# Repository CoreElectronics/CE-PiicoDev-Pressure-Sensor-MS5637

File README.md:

# PiicoDev® Pressure Sensor MS5637

This is the repo for the Core Electronics [PiicoDev Pressure Sensor](https://core-electronics.com.au/catalog/product/view/sku/CE07832).

Our PiicoDev® Pressure Sensor is perfect for measuring barometric pressure or infering altitude from air pressure - the on-board MS5637 is capable of measuring differences as small as 13cm! The accurate, MEMs pressure sensor is very sensitive, factory calibrated, low power and easy to use - forfect for home weather stations, detecting changes in altitude or pneumatic-based control projects.

**Features**

- Accurate air pressure measurements
- PiicoDev connector, compatible with Qwiic and STEMMA QT (3.3V only)
- 2.54mm breakout for breadboarding/prototyping
- Manufactured and [supported](https://core-electronics.com.au/contacts/) in Australia by Core Electronics
- [Getting Started Guides](https://core-electronics.com.au/catalog/product/view/sku/CE07832#guides)

**Technical Specifications**

- I2C address: 0x76
- Dimensions: 25.4x25.4mm
- Mounting Holes: 2x M2.5
- MS5637:
  - Operating range: 300 to 1200 hPa, -40 to 85°C
  - Error band at 25°C: ±2 hPa

## License
This project is open source - please review the LICENSE.md file for further licensing information.

If you have any technical questions, or concerns about licensing, please contact technical support on the [Core Electronics forums](https://forum.core-electronics.com.au/).

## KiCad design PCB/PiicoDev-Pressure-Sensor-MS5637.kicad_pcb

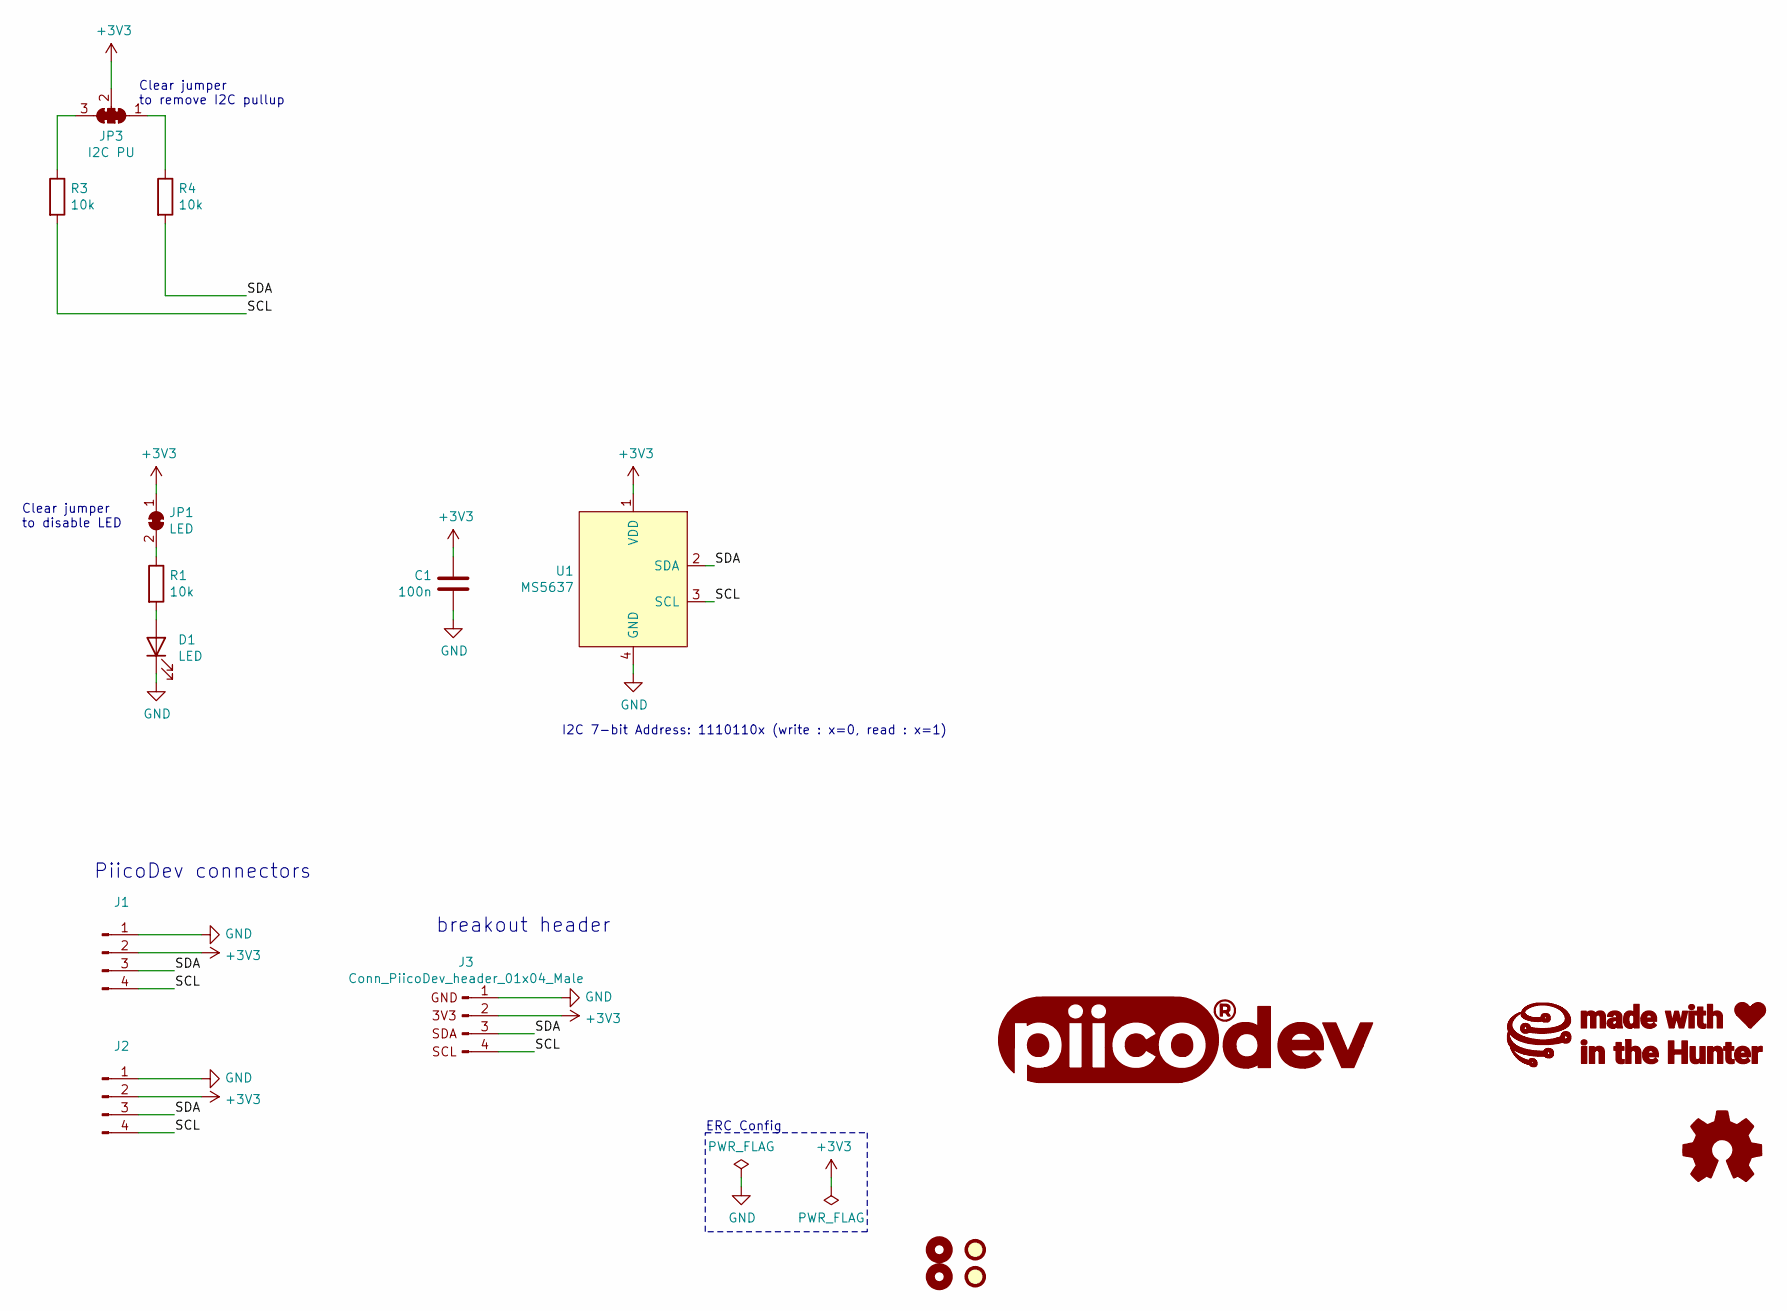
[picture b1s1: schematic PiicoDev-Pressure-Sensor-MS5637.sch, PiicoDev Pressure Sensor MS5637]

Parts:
C1: 100n; C_0402_1005Metric
D1: LED; LED_0603_1608Metric
FID1, FID2: Fiducial; Fiducial_1mm_Mask2mm
G1: LOGO_CoreElectronics_no-text; CoreElectronics_logo_5mm
G2: LOGO_piico; piicodev_logo_14.2x3.4mm
G3: LOGO_made-with-love; piicodev_logo_14.2x3.4mm
H1, H4: MountingHole; MountingHole_2.7mm_M2.5_PadClearance_1.2
J1, J2: JST_SH_SM04B-SRSS-TB_1x04-1MP_P1.00mm_Horizontal
J3: Conn_PiicoDev_header_01x04_Male; PiicoDev_header_4pin
JP1: LED; SolderJumper-2_P1.3mm_Bridged_RoundedPad1.0x1.5mm
JP3: I2C PU; SolderJumper-3_P1.3mm_Closed_RoundedPad1.0x1.5mm_NumberLabe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
LOGO1: Logo_Open_Hardware_Small; oshw
R1, R3, R4: 10k; R_0402_1005Metric
U1: MS5637; TE_MS5637

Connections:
+3V3: C1.2, J1.2, J2.2, J3.2, JP1.1 (A), JP3.2 (C), U1.1 (VDD)
/SCL: J1.4, J2.4, J3.4, R3.2, U1.3 (SCL)
/SDA: J1.3, J2.3, J3.3, R4.2, U1.2 (SDA)
GND: C1.1, D1.1 (K), J1.1, J2.1, J3.1, U1.4 (GND)
unnamed: D1.2 (A), R1.2
unnamed: JP1.2 (B), R1.1
unnamed: JP3.1 (A), R4.1
unnamed: JP3.3 (B), R3.1

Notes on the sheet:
Clear jumper to disable LED
Clear jumper to remove I2C pullup
PiicoDev connectors
breakout header
I2C 7-bit Address: 1110110x (write : x=0, read : x=1)
ERC Config

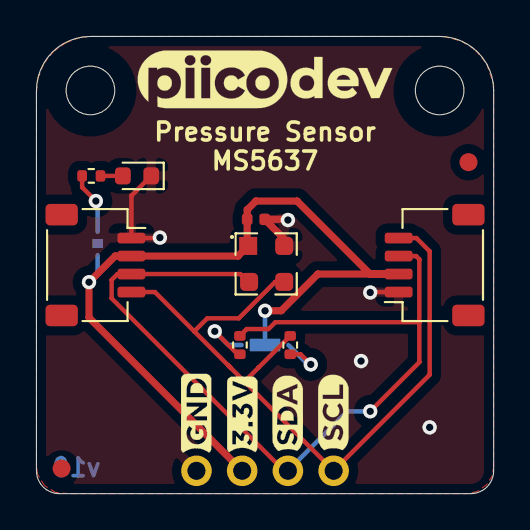
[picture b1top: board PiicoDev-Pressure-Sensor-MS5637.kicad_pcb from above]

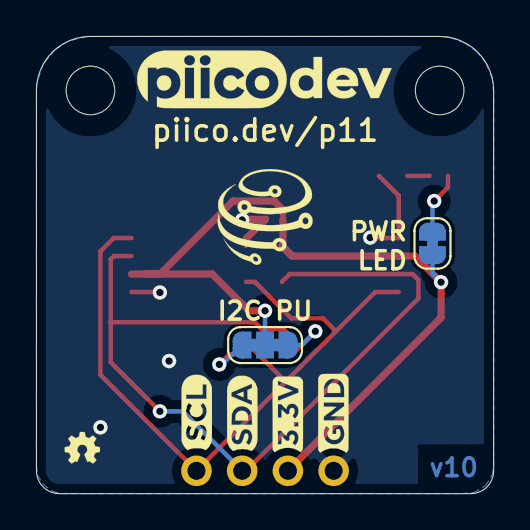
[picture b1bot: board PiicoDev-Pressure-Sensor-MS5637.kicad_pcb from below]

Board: 2 copper layers, 25.4 x 25.4 mm, 19 parts (6 on the bottom side), 8 nets.

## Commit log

2022-01-11 Change 4k7 resistors to 10k

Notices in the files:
PCB/PiicoDev-Pressure-Sensor-MS5637.kicad_pcb:
License: CCASAv4.0 http://creativecommons.org/licenses/by-sa/4.0
